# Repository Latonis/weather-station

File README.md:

# weather-station

This repoistory holds my current project for designing a home monitoring solution for temperature, humidity, and eventually the status of the plants in my office. Eventually, I would like to use an ESP32 or similar Wi-Fi enabled chip to host a small webserver or send notifications to alert me when desired specifications are met.

## Features
- measure temperature in Fahrenheit
- measure humidity
- display these measurements visually

## Goal Features
- measure soil moisture
- alert when soil is too dry
- alert when temperature is below a set value
- alert when temperature is above a set value
- alert when humidity is above a set value

# Parts List (continually updated)
- Arduino Nano (Atmega 168P)
- LCD1602 Module
- DHT11 Sensor
- Many jumper wires (for the time being)

# Schematic
All of the schematics can be found in the [`sch/`](sch/) directory.

# Code

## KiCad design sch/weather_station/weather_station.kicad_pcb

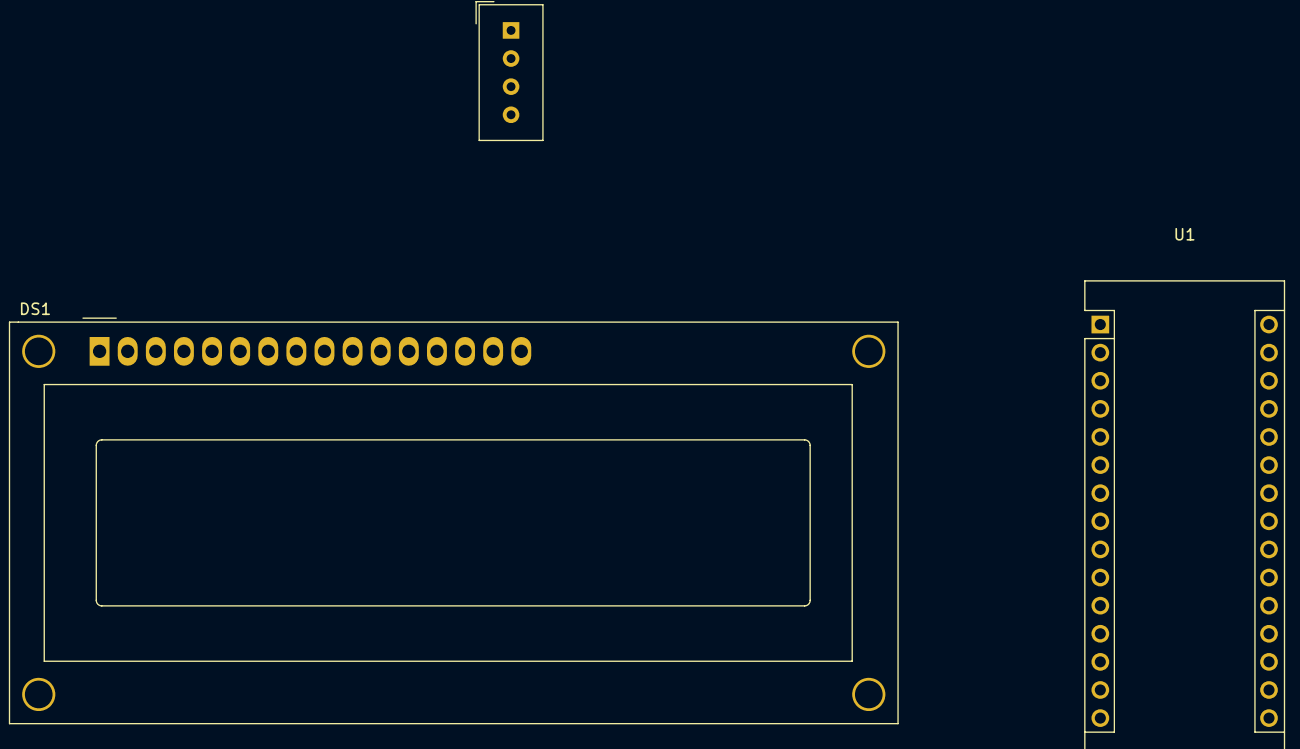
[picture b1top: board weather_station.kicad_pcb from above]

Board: 2 copper layers, 3 parts (0 on the bottom side), 2 nets, no tracks yet.

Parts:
DS1: WC1602A
U1: Arduino_Nano_Atmega168pa; Arduino_nano_clone
U2: DHT11; Aosong_DHT11_5.5x12.0_P2.54mm

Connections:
+5V: DS1.2 (VDD), U2.1 (VCC)
Earth: DS1.1 (VSS), DS1.3 (VO), DS1.5 (R/W), DS1.16 (LED(-)), U2.4 (GND)

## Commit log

2022-05-01 initial project commit
2022-05-01 temperature working
2022-05-01 lcd beginning
2022-05-01 LCD functioning
2022-05-01 cleanup
2022-05-01 working through Kicad
